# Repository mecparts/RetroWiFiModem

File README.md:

# Retro WiFi modem

## An ESP8266 based RS232 \<-\> WiFi modem with Hayes AT style commands and LED indicators

### (And yes, this version makes the noises)

This project grew out of a desire to get an old Ampro LB+/Z80 hooked up
to the Internet.

Right from the start, I knew I wanted a row of LED indicators at the
front of the modem so that it would be reminiscent of an old Hayes
Smartmodem. (I briefly considered finding an old Smartmodem on eBay, but
soon remembered that the case had in fact been made of metal; they don't
build 'em like that anymore.)

Since the modem was going to be hooked up to the Little Board's
serial port, I needed an actual RS-232 level serial port, with either a
DB-25 or DE-9 connector.

And finally, since I wanted the Hayes style LEDs, I thought it would be
handy to have the Hayes AT commands too, at least as close as I could
manage.

That was all I started with. I couldn't tell you how I stumbled across
the whole WiFi modem thing; I can't even remember what terms I searched
with but very quickly I came across the message thread at [WiFi232's
Evil
Clone](http://www.vcfed.org/forum/entry.php?740-WiFi232-s-Evil-Clone&bt=1056).
Inspired by that, and [Paul Rickards'
WiFi232](http://biosrhythm.com/?page_id=1453), and [Daniel Jameson's
ESP8266 based virtual modem](https://github.com/stardot/esp8266_modem) I
got started.

I had a preliminary version put together and working by the first
evening. Then the wholesale changes to the software began. And for the
longest time, it looked like they'd never end. Eventually though, they
calmed down and "wholesale changes" downshifted to "another tweak I'd
like to make."

The hardware didn't change nearly as much from beginning to end. I did
the development on a Wemos D1 R1 and a little half length solderless
breadboard mounted together. The plan for the final hardware was always
to use a [Wemos D1 mini](https://docs.wemos.cc/en/latest/d1/d1_mini.html).
A MAX3237 took care of the 3.3V <-> RS-232 level shifting, and a
74HCT245 was used to drive the indicator LEDs.

The only major additions to the hardware during development was an OR
gate on the serial output from the ESP8266 and the addition of a
DFPlayer Mini for the dialing and connection sounds.

On startup, the ESP8266 sends out some debug information
(at an oddball baud rate) through the serial port. It shows up as
garbage characters to whatever's hooked up to the serial port. It
annoyed me enough that I fed the Tx signal through the OR gate, with the
other input hooked up to an output pin that I could count on remaining
high (thereby masking off the Tx signal) until after the sketch had
started and set it low.

And while it didn't make the cut the first time around, there's a
DFPlayer Mini in this version for faux dialing and connection sounds.
They really do complete the whole retro feel (but they can be turned off
too).

## The Hardware

The second time around, I decided that I was going to bite the bullet
and go with some surface mount stuff, starting with the MAX3237. Having
a full suite of RS-232 control signals seemed worth it. I stuck with
through hole components where I could (I already had most of them in my
parts box) but adding the DFPlayer Mini meant that the 74HC32 and
74HCT245 had to be surface mount just to make them fit.

In keeping with the retro theme, the modem uses classic Hayes style
blinking LEDs and a DE-9F for the RS-232 connector. Everything is
displayed and brought out to the DE-9F connector: RTS, CTS, DSR, DTR,
DCD, RI, TxD and RxD.

The PCB is laid out for a
[Wemos D1 mini](https://docs.wemos.cc/en/latest/d1/d1_mini.html) and the
software expects to see just that. If you're just using the software and
not the PCB, there's no reason you couldn't use another kind of ESP8266
board; I used a D1 R1 myself when I was developing the modem. You'd just
need to add pin definitions for your board in RetroWiFiModem.h.

A separate 3.3V regulator is used to power the MAX3232 IC and 74HC32
quad OR gate. Some (most?) D1 mini clones have the smallest 3.3V
regulator on board that they can get away with to power the board, and
they don't have a lot of mA's left over to power anything else. Better
safe than sorry.

The power connector expects a 2.1mm I.D. x 5.5mm O.D. barrel plug,
delivering 5 volts, centre positive.  I used a Tri-Mag L6R06H-050 (5V,
1.2A), [DigiKey part#
364-1251-ND](https://www.digikey.com/product-detail/en/tri-mag-llc/L6R06H-050/364-1251-ND/7682614).
If you plug in a 9V adapter like you'd use for an Arduino, you *will*
let the magic smoke out and have an ex-modem on your hands.

On the off chance that there's someone else out there with a well
stocked parts box and a burning desire to put together their own WiFi
modem, there's a [BOM](kicad/RetroWiFiModem-bom.csv) in the kicad
sub directory. If you actually had to go out and buy all the parts, it
really wouldn't be cost effective.

Then again, how practical is getting an Ampro Little Board on the
Internet? Practicality isn't always everything. Sometimes nostalgia is
worth the effort.

## The case

Like I said at the start, I would have loved to have used an old Hayes
Smartmodem case, but they were metal and wouldn't have allowed the WiFi
to work particularly well.

In the end I went with a Hammond 1593N case (DigiKey part #
[HM963-ND](https://www.digikey.com/en/products/detail/hammond-manufacturing/1593NBK/1090774)
or [HM964-ND](https://www.digikey.com/en/products/detail/hammond-manufacturing/1593NGY/1090775)
depending on whether you like black or grey). STL and OpenSCAD
files are included for the front and back panels. You could use the
proper Hammond red panel for the front (DigiKey part #
[HM965-ND](https://www.digikey.com/en/products/detail/hammond-manufacturing/1593NIR10/1090776)),
*but* they're only available in 10 packs and their price is highway robbery.
I ended up using a slightly smaller red panel (DigiKey part #
[HM889-ND](https://www.digikey.com/en/products/detail/hammond-manufacturing/1593SIR10/409899))
that was ~much~ cheaper (it has recently increased in price by 500%)
and available in single units.

The labels are unbelievably low tech. I print them on a piece of inkjet
transparency film. I then cut that down to size so that it will fit
under the LED opening. Then I attach the trimmed down transparency piece
to a length of matte finish, invisible tape and carefully position it in
place. A bit of careful work with an x-acto knife and you've got
yourself a label that looks like it's part of the panel. If you look
closely at the front panel image you can see the edges of the
transparency film and the tape, but in practice they both essentially
disappear.

## The PCB

The PCB includes cutouts for the two columns that join the case
together, and mounting holes for the 6 standoffs. Also, there's an oddly
shaped cutout in back end to allow a particular IDC DE-9F I had on hand.
It's available from DigiKey (or a very close clone is) but it's fairly
pricey. But there's plenty of room for an ordinary solder cup DE-9F.
You'd most likely want to omit the 10 pin header and just wire the DE-9F
right to the board.

## The Software

In a nod to its popularity, the command set I used largely follows that
used in [Paul Rickards' WiFi232](http://biosrhythm.com/?page_id=1453)
modem. Even if the innards are completely different, it made sense to
make it *work* like what people were already used to. There's a reason
everyone's been copying the Hayes command set for almost 40 years!

### First time setup

The default serial configuration is 9600bps, 8 data bits, no parity, 1
stop bit.

Here's the commands you need to set up the modem to automatically
connect to your WiFi network:

1. `AT$SSID=your WiFi network name` to set the WiFi network that the
modem will connect to when it powers up.
2. `AT$PASS=your WiFi network password` to set the password for the
network.
3. `ATC1` to connect to the network.
4. Optional stuff:
   * `AT$SB=speed` to set the default serial speed.
   * `AT$SU=dps` to set the data bits, parity and stop bits.
   * `ATNETn` to select whether or not to use Telnet protocol.
   * `AT&Kn` to use RTS/CTS flow control or not.
   * `AT&Dn` to set up DTR handling.
5. `AT&W` to save the settings.

Once you've done that, the modem will automatically connect to your WiFi
network on power up and will be ready to "dial up" a connection with
ATDT.

### Command Reference

Multiple AT commands can be typed in on a single line. Spaces between
commands are allowed, but not within commands (i.e. AT S0=1 X1 Q0 is
fine; ATS 0=  1 is not). Commands that take a string as an argument
(e.g. AT$SSID=, AT$TTY=) assume that *everything* that follows is a part
of the string, so no commands are allowed after them.

Command | Details
------- | -------
+++     | Online escape code. Once your modem is connected to another device, the only command it recognises is an escape code of a one second pause followed by three typed plus signs and another one second pause, which puts the modem back into local command mode. The character used can be set with `ATS2=n`.
A/      | Repeats the last command entered. Do not type AT or press Enter.
AT      | The attention prefix that precedes all command except A/ and +++.
AT?     | Displays a help cheatsheet.
ATA     | Force the modem to answer an incoming connection when the conditions for auto answer have not been satisfied.
ATC?<br>ATC*n* | Query or change the current WiFi connection status. A result of 0 means that the modem is not connected to WiFi, 1 means the modem is connected. The command ATC0 disconnects the modem from a WiFi connection. ATC1 connects the modem to the WiFi.
ATDS*n* | Calls the host specified in speed dial slot *n* (0-9).
ATDT<i>[+=-]host[:port]</i> | Tries to establish a WiFi TCP connection to the specified host name or IP address. If no port number is given, 23 (Telnet) is assumed. You can also use ATDT to dial one of the speed dial slots in one of two ways:<br><br><ul><li>The alias in each speed dial slot is checked to see if it matches the specified hostname.</li><li>A host specified as 7 identical digits dials the slot indicated by the digit. (i.e. 2222222 would speed dial the host in slot 2).</li></ul>Preceding the host name or IP address with a +, = or - character overrides the ATNET setting for the period of the connection.<br><br><ul><li>**+** forces NET2 (fake Telnet)</li><li>**=** forces NET1 (real Telnet)</li><li>**-** forces NET0 (no Telnet)</li></ul>Once the dial attempt has begun, pressing any key before the connection is established will abort the attempt.
ATE?<br>ATE*n* | Command mode echo. Enables or disables the display of your typed commands.<br><br><ul><li>E0 Command mode echo OFF. Your typing will not appear on the screen.</li><li>E1 Command mode echo ON. Your typing will appear on the screen.</li></ul>
ATGET*http&#58;//host[/page]* | Displays the contents of a website page. **https** connections are not supported. Once the contents have been displayed, the connection will automatically terminate.
ATH | Hangs up (ends) the current connection.
ATI | Displays the current network status, including sketch build date, WiFi and call connection state, SSID name, IP address, and bytes transferred.
ATL?<br>ATL*n* | Query or set the volume of the speaker (0-3).
ATM?<br>ATM*n* | Query or set whether the speaker is enabled or disabled. ATM0 disables the speaker. ATM1 enables it.
ATNET?<br>ATNET*n* | Query or change whether telnet protocol is enabled. A result of 0 means that telnet protocol is disabled; 1 is *Real* telnet protocol and 2 is *Fake* telnet protocol. If you are connecting to a telnet server, it may expect the modem to respond to various telnet commands, such as terminal name (set with `AT$TTY`), terminal window size (set with `AT$TTS`) or terminal speed. Telnet protocol should be enabled for these sites, or you will at best see occasional garbage characters on your screen, or at worst the connection may fail.<br><br>The difference between *real* and *fake* telnet protocol is this: with *real* telnet protocol, a carriage return (CR) character being sent from the modem to the telnet server always has a NUL character added after it. The implementation of the telnet protocol used by some BBSes doesn't properly strip out the NUL character. When connecting to such BBSes (Particles! is one), use *fake* telnet.<br><br>When using *real* telnet protocol, when the telnet server sends a CR character followed by a NUL character, only the CR character will be sent to the serial port; the NUL character will be silently stripped out. With *fake* telnet protocol, the NUL will be passed through.
ATO | Return online. Use with the escape code (+++) to toggle between command and online modes.
ATQ?<br>ATQ*n* | Enable or disable the display of result codes. The default is Q0.<br><br><ul><li>Q0 Display result codes.</li><li>Q1 Suppress result codes (quiet).</li></ul>
ATRD<br>ATRT | Displays the current UTC date and time from NIST in the format *YY-MM-DD HH:MM:SS*. A WiFi connection is required and you cannot be connected to another site.
ATS0?<br>ATS0=*n* | Display or set the number of "rings" before answering an incoming connection. Setting `S0=0` means "don't answer".
ATS2?<br>ATS2=*n* | Display or set the ASCII code used in the online escape sequence. The default value is 43 (the + plus character). Setting it to any value between 128 and 255 will disable the online escape function.
ATV?<br>ATV*n* | Display result codes in words or numbers. The default is V1.<br><br><ul><li>V0 Display result codes in numeric form.</li><li>V1 Display result codes in text form.</li></ul>
ATX?<br>ATX*n* | Control the amount of information displayed in the result codes. The default is X1 (extended codes).<br><br><ul><li>X0 Display basic codes (CONNECT, NO CARRIER)</li><li>X1 Display extended codes (CONNECT speed, NO CARRIER (connect time))</li></ul>
ATZ | Resets the modem.
AT&F | Reset the NVRAM contents and current settings to the sketch defaults. All settings, including SSID name, password and speed dial slots are affected.
AT&D?<br>AT&D*n* | Display or set the handling of DTR going inactive. The default is &D0 (ignored).<br><br><ul><li>&D0 Ignore</li><li>&D1 Go to command mode</li><li>&D2 End call</li><li>&D3 Reset modem</li></ul>
AT&K?<br>AT&K*n* | Data flow control. Prevents the modem's buffers for received and transmitted from overflowing.<br><br><ul><li>&K0 Disable data flow control.</li><li>&K1 Use hardware flow control. Requires that your computer and software support Clear to Send (CTS) and Request to Send (RTS) at the RS-232 interface.</li></ul>
AT&R?<br>AT&R=*server pwd* | Query or change the password for incoming connections. If set, the user has 3 chances in 60 seconds to enter the correct password or the modem will end the connection.
AT&V*n* | Display current or stored settings.<br><br><ul><li>&V0 Display current settings.</li><li>&V1 Display stored settings.</li></ul>
AT&W | Save current settings to NVRAM.
AT&Zn?<br>AT&Z*n*=*host[:port],alias* | Store up to 10 numbers in NVRAM, where *n* is the position 0-9 in NVRAM, and *host[:port]* is the host string, and *alias* is the speed dial alias name. The host string may be up to 50 characters long, and the alias string may be up to 16 characters long.<br><br>Example: `AT&Z2=particlesbbs.dyndns.org:6400,particles`<br><br>This number can then be dialed in any of the following ways:<br><br><ul><li>`ATDS2`</li><li>`ATDTparticles`</li><li>`ATDT2222222`</li></ul>
AT$AE?<br>AT$AE=*startup AT cmd* | Query or change the command line to be executed when the modem starts up.
AT$AYT | Sends a Telnet "Are You There?" command if connected to a Telnet remote.
AT$BM?<br>AT$BM=*server busy msg* | Query or change a message to be returned to an incoming connection if the modem is busy (i.e. already has a connection established).
AT$MDNS<br>AT$MDNS=*mDNS name* | Query or change the mDNS network name (defaults to "espmodem"). When a non zero TCP port is defined, you can telnet to that port with **telnet mdnsname.local port**.
AT$PASS?<br>AT$PASS=*WiFi pwd* | Query or change the current WiFi password. The password is case sensitive. Clear the password by issuing the set command with no password. The maximum length of the password is 64 characters.
AT$SB?<br>AT$SB=*n* | Query or change the current baud rate. Valid values for "n" are 110, 300, 450, 600, 710, 1200, 2400, 4800, 9600, 19200, 38400, 57600, 76800 and 115200. Any other value will return an ERROR message. The default baud rate is 1200. The Retro WiFi modem does not automatically detect baud rate like a dial-up modem. The baud rate setting must match that of your terminal to operate properly. It will display garbage in your terminal otherwise.
AT$SP?<br>AT$SP=*n* | TCP server port to listen on. A value of 0 means that the TCP server is disabled, and no incoming connections are allowed.
AT$SSID?<br>AT$SSID=*ssid name* | Query or change the current SSID to the specified name. The given SSID name is case sensitive. Clear the SSID by issuing the set command with no SSID. The maximum length of the SSID name is 32 characters.
AT$SU?<br>AT$SU=*dps* | Query or change the current number of data bits ('d'), parity ('p') and stop bits ('s") of the serial UART. Valid values for 'd' are 5, 6, 7 or 8 bits. Valid values for 'p' are (N)one, (O)dd or (E)ven parity. Valid values for 's' are 1 or 2 bits. The default settings are 8N1. The UART setting must match your terminal to work properly.
AT$TTL?<br>AT$TTL=*telnet location* | Query or change the Telnet location value to be returned when the Telnet server issues a SEND-LOCATION request. The default value is "Computer Room".
AT$TTS?<br>AT$TTS=*WxH* | Query or change the window size (columns x rows) to be returned when the Telnet server issues a NAWS (Negotiate About Window Size) request. The default value is 80x24. For terminals that are smaller than 80x24, setting these values appropriately will enable paging on the help (AT?) and network status (ATI) commands.
AT$TTY?<br>AT$TTY=*terminal type* | Query or change the terminal type to be returned when the Telnet server issues a TERMINAL-TYPE request. The default value is "ansi".
AT$W?<br>AT$W=*n* | Startup wait.<br><br><ul><li>$W=0 Startup with no wait.</li><li>$W=1 Wait for the return key to be pressed at startup.</li></ul>

### Updating the Software

While I liked the idea of being able to update the software OTA, it
seemed to make more sense in my situation to be able to *push* a new
version as I built it rather than have the modem *pull* it. So that's
what I did. It uses the default OTA upload capability built into the
Arduino IDE.

**Jan 24/22:** It's been reported that the ESP8266 core is slightly
snafu'd at the moment, and that it's breaking things in the modem
software. As a workaround, I've added the bin file that gets uploaded
to the modem in the repository. I haven't updated my ESP8266 core in
ages; "if it isn't broken, don't break it", and everything still works
for me. The bin file can be uploaded with the *espota.py* tool in the
ESP8266 tool directory tree.

(If TPTB have deleted/renamed/moved that tool in the current core,
you'll have to figure out how to do a manual OTA update.)

### RTS/CTS handshaking and a dead spin loop issue

Something I noticed with ESP8266 software that puzzled me was the
number of places I saw a series of Serial print statements being broken
up with calls to yield(), like so:

```
   Serial.print("Hello world!\n");
   yield();
   Serial.print("How are you today?\n");
   yield();
```
It didn't take long to figure out what was going on; The print() call
was blocking, and at lower baud rates, even printing a few relatively
short strings was enough to cause the watchdog to bark and cause a
reset. So the repetitive yield() calls were an attempt to feed the
watchdog often enough to keep it from barking.

What does this have to do with RTS/CTS handshaking? Simply put,
lowering RTS for more than a few seconds was causing the watchdog to
bark as well. So I started digging.

In cores/esp8266/uart.cpp I found the following function:

```
static void
uart_do_write_char(const int uart_nr, char c)
{
    while(uart_tx_fifo_full(uart_nr));

    USF(uart_nr) = c;
}
```

This is the low level function that everything calls to send a character
out the serial port. The cause of the watchdog barking is in the dead
spin while loop. It waits until there's room in the transmit FIFO to add
another character. So if RTS/CTS handshaking is enabled, and RTS is low
for longer than the watchdog likes: woof.

What I did to quiet the watchdog down both when sending long strings at
low baud rates and during long waits for RTS to come active again was to
add a yield() call to the dead spin while loop, like so:

```
static void
uart_do_write_char(const int uart_nr, char c)
{
    while(uart_tx_fifo_full(uart_nr))
      yield();

    USF(uart_nr) = c;
}
```

This way, no matter how long the code has to wait for space in the
transmit FIFO, the watchdog is kept well fed and quiet.

## Status

As I said way back in 2020, is a personal project like this ever
*really* finished? I've had two units assembled and in use since the
spring of 2020, and a third since 2022, and while there's
been some software changes since then, and a second rev of the hardware
to bring out all the RS-232 control signals and add in the faux dialing
and connections sounds, I really don't expect any more changes. But I've
said that before! There are no outstanding bugs that I'm aware of, and
no new features on my wish list. For the time being at least, I think
it's complete.

### Linux, Telnet, Zmodem and downloading binary files

Have you used the modem to 'dial' into a Linux box? And have you done a
`sz binary_file` on the Linux box? And at a completely reproducible
point in the file, has the connection dropped? But other binary files
work just fine? Then read on.

This drove me slightly batty for months. I finally narrowed it down to
trying to send blocks of binary data with a large number of FF bytes. I
eventually created a test file consisting of 2K of FF and used that to
test with. I could download it through the modem with Xmodem just fine.
Ymodem also worked if I kept the block size down to 128 bytes - but the
connection would drop instantly if I tried sending 1K blocks. Same thing
with Zmodem.

In fact, if I just tried `cat binary_file`, the connection would
drop. Which eventually got me thinking. Sitting at the console on my
main Linux box, I telnet'd to the same box and logged in. No WiFi modem
involved anywhere, just a telnet session on the console to the same box.
I then did a `cat binary_file`. The telnet connection dropped, and I
was back in my original session.

It's the Linux telnet daemon. Not the modem at all.

To prove it to myself, I hooked up WiFi modems to two systems on their
serial ports and had one dial into the other. I could send the all FF
binary file back and forth with Zmodem and Ymodem, no trouble at all.

But you really, really need to download that binary file through the
modem from a telnet connection to a Linux box? You're not going to be
able to use Zmodem. Ymodem will work (the sy command defaults to 128
byte blocks), as will Xmodem. But not Zmodem.

Oddly enough, the telnet daemon has no trouble *receiving* the all FF
binary file. Only sending it. Your guess as to why is probably better
than mine.

## References

* [WiFi232 - An Internet Hayes Modem for your Retro Computer](http://biosrhythm.com/?page_id=1453)<br>
* [WiFi232's Evil Clone](https://forum.vcfed.org/index.php?threads/wifi232s-evil-clone.1070412/)<br>
* [Jussi Salin's Virtual modem for ESP8266](https://github.com/jsalin/esp8266_modem)<br>
* [Stardot's ESP8266 based virtual modem](https://github.com/stardot/esp8266_modem)<br>
* [Roland Juno's ESP8266 based virtual modem](https://github.com/RolandJuno/esp8266_modem)

## Acknowledgements

* A whole lot of people owe a big vote of thanks to Jussi Salin for
releasing their virtual modem code for the ESP8266 and starting the
ball rolling.
* Paul Rickards for an amazing bit of hardware to draw inspiration from.
* All the Stardot contributors for their work.
* And, of course, Dennis C. Hayes for creating something so simple and
elegant that has stood the test of time.

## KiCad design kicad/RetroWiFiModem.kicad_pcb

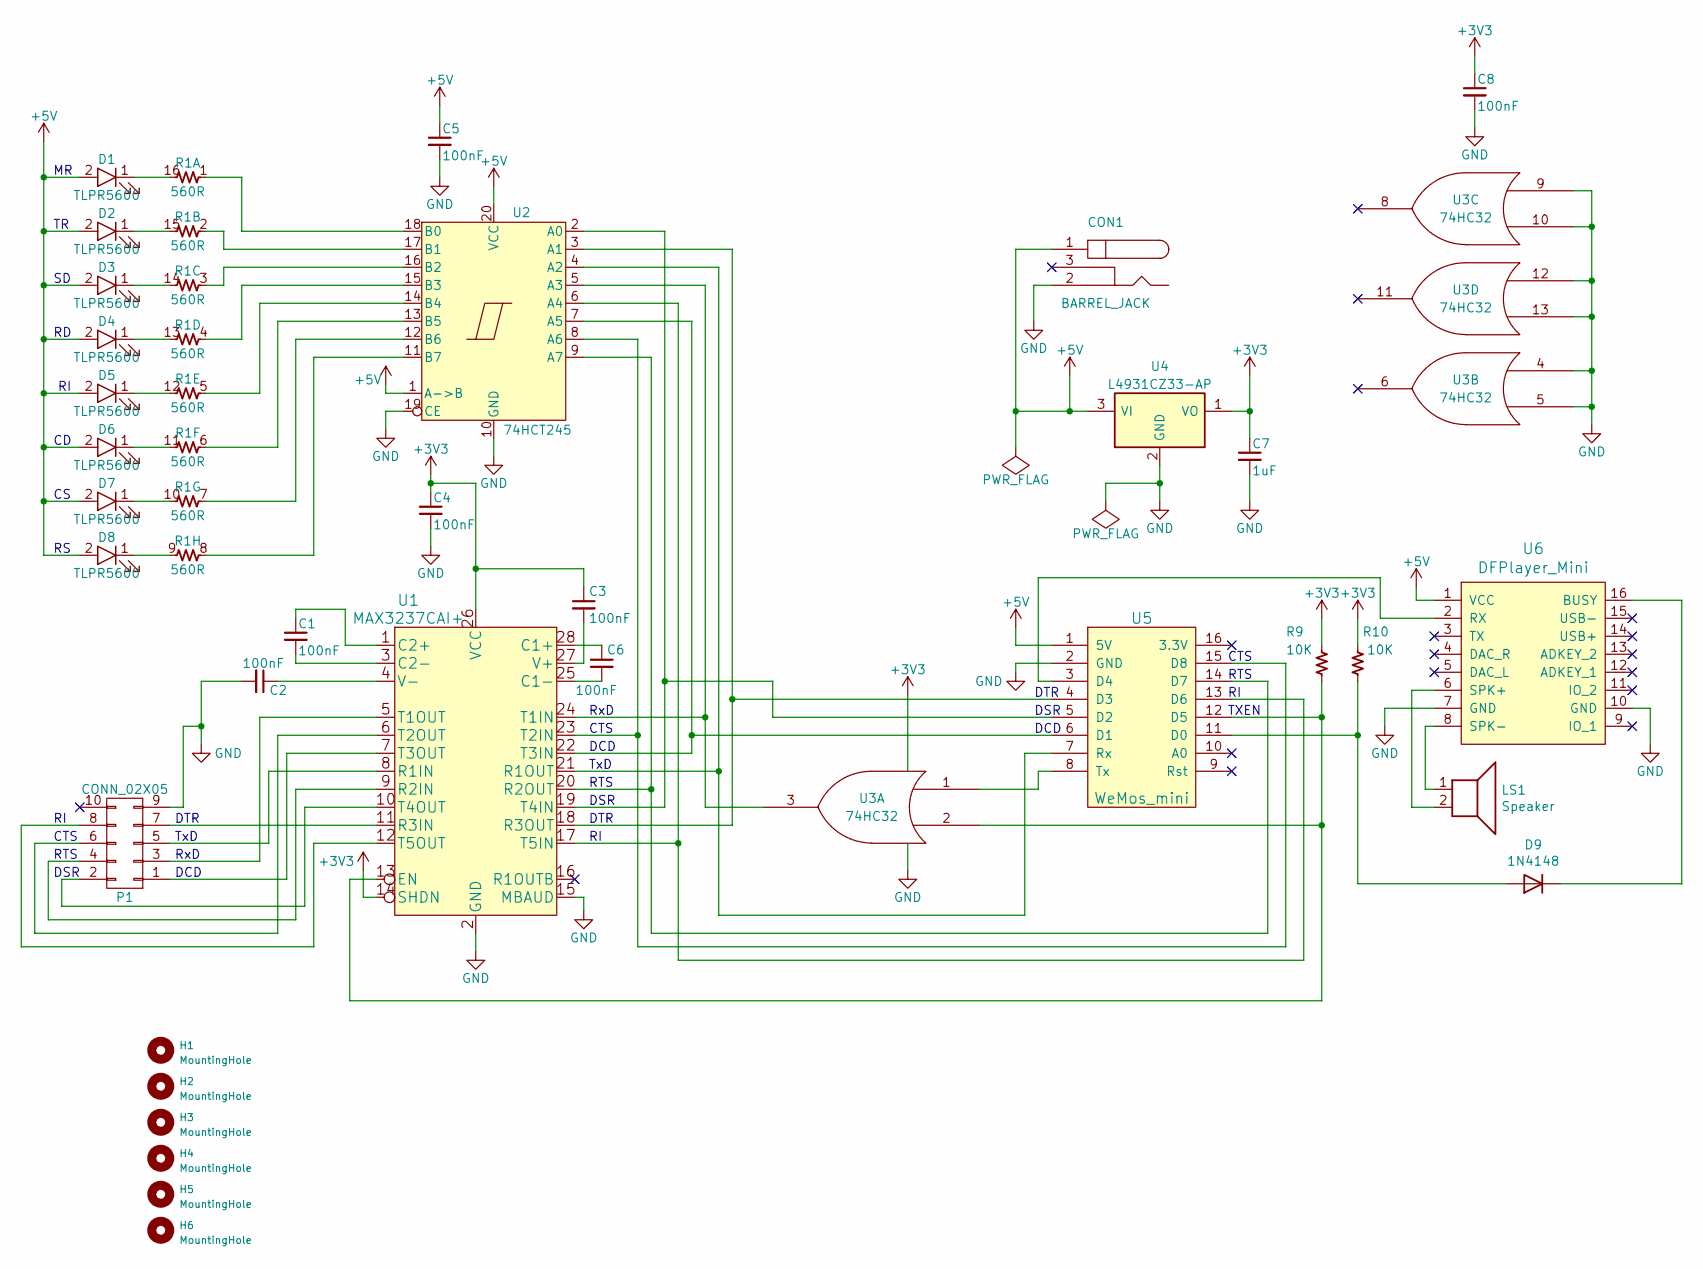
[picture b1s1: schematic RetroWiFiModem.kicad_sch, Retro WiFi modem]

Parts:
C1, C2, C3, C4, C5, C8: 100nF; C_Disc_D3_P2.5; DigiKey PN 399-9859-1-ND
C6: 100nF; R3; DigiKey PN 399-9843-ND
C7: 1uF; C_Disc_D3_P2.5; DigiKey PN 399-3529-ND
CON1: BARREL_JACK; BarrelJack_Horizontal; DigiKey PN 839-54-00166-ND
D1, D2, D3, D4, D5, D6, D7, D8: TLPR5600; LED-3MM; DigiKey PN TLPR5600-ND
D9: 1N4148; D_DO-35_SOD27_P7.62mm_Horizontal
H1, H2, H3, H4, H5, H6: MountingHole; MountingHole_3.2mm
LS1: Speaker; PinHeader_1x02_P2.54mm_Vertical
P1: CONN_02X05; IDC_Header_Straight_10pins; DigiKey PN ED1543-ND
R1: 560R; DIP-16_W7.62mm_LongPads; DigiKey PN CF18JT560RCT-ND
R9, R10: 10K; R3; DigiKey PN CF18JT10K0CT-ND
U1: MAX3237CAI+; SOIC-28W_7.5x17.9mm_Pitch1.27mm
U2: 74HCT245; SOIC-20W_7.5x12.8mm_P1.27mm
U3: 74HC32; SOIC-14_3.9x8.7mm_P1.27mm; DigiKey PN 296-1589-5-ND
U4: L4931CZ33-AP; TO-92_Inline_Wide; DigiKey PN LP2950ACZ-3.3GOS-ND
U5: WeMos_mini; wemos-d1-mini-with-pin-header-and-connector
U6: DFPlayer_Mini; DFPlayerMini

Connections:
+3V3: C3.1, C4.1, C7.1, C8.1, R9.1, R10.1, U1.14 (SHDN), U1.26 (VCC), U3.14 (VCC), U4.1 (VO)
+5V: C5.1, CON1.1, D1.2 (A), D2.2 (A), D3.2 (A), D4.2 (A), D5.2 (A), D6.2 (A), D7.2 (A), D8.2 (A), U2.1 (A->B), U2.20 (VCC), U4.3 (VI), U5.1 (5V), U6.1 (VCC)
GND: C2.2, C4.2, C5.2, C7.2, C8.2, CON1.2, P1.9, U1.2 (GND), U1.15 (MBAUD), U2.10 (GND), U2.19 (CE), U3.4, U3.5, U3.7 (GND), U3.9, U3.10, U3.12, U3.13, U4.2 (GND), U5.2 (GND), U6.7 (GND), U6.10 (GND)
unnamed: C1.1, U1.1 (C2+)
unnamed: C1.2, U1.3 (C2-)
unnamed: C2.1, U1.4 (V-)
unnamed: C3.2, U1.27 (V+)
unnamed: C6.1, U1.28 (C1+)
unnamed: C6.2, U1.25 (C1-)
unnamed: D1.1 (K), R1.16 (R1.2)
unnamed: D2.1 (K), R1.15 (R1.2)
unnamed: D3.1 (K), R1.14 (R1.2)
unnamed: D4.1 (K), R1.13 (R1.2)
unnamed: D5.1 (K), R1.12 (R1.2)
unnamed: D6.1 (K), R1.11 (R1.2)
unnamed: D7.1 (K), R1.10 (R1.2)
unnamed: D8.1 (K), R1.9 (R1.2)
unnamed: D9.1 (K), U6.16 (BUSY)
unnamed: D9.2 (A), R10.2, U5.11 (D0)
unnamed: LS1.1, U6.8 (SPK-)
unnamed: LS1.2, U6.6 (SPK+)
unnamed: P1.1, U1.7 (T3OUT)
unnamed: P1.2, U1.10 (T4OUT)
unnamed: P1.3, U1.5 (T1OUT)
unnamed: P1.4, U1.9 (R2IN)
unnamed: P1.5, U1.8 (R1IN)
unnamed: P1.6, U1.6 (T2OUT)
unnamed: P1.7, U1.11 (R3IN)
unnamed: P1.8, U1.12 (T5OUT)
unnamed: R1.1 (R1.1), U2.18 (B0)
unnamed: R1.2 (R1.1), U2.17 (B1)
unnamed: R1.3 (R1.1), U2.16 (B2)
unnamed: R1.4 (R1.1), U2.15 (B3)
unnamed: R1.5 (R1.1), U2.14 (B4)
unnamed: R1.6 (R1.1), U2.13 (B5)
unnamed: R1.7 (R1.1), U2.12 (B6)
unnamed: R1.8 (R1.1), U2.11 (B7)
unnamed: R9.2, U1.13 (EN), U3.2, U5.12 (D5)
unnamed: U1.17 (T5IN), U2.6 (A4), U5.13 (D6)
unnamed: U1.18 (R3OUT), U2.3 (A1), U5.4 (D3)
unnamed: U1.19 (T4IN), U2.2 (A0), U5.5 (D2)
unnamed: U1.20 (R2OUT), U2.9 (A7), U5.14 (D7)
unnamed: U1.21 (R1OUT), U2.4 (A2), U5.7 (Rx)
unnamed: U1.22 (T3IN), U2.7 (A5), U5.6 (D1)
unnamed: U1.23 (T2IN), U2.8 (A6), U5.15 (D8)
unnamed: U1.24 (T1IN), U2.5 (A3), U3.3
unnamed: U3.1, U5.8 (Tx)
unnamed: U5.3 (D4), U6.2 (RX)

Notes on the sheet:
DCD
CTS
DSR
TxD
DTR
RxD
RTS
TXEN

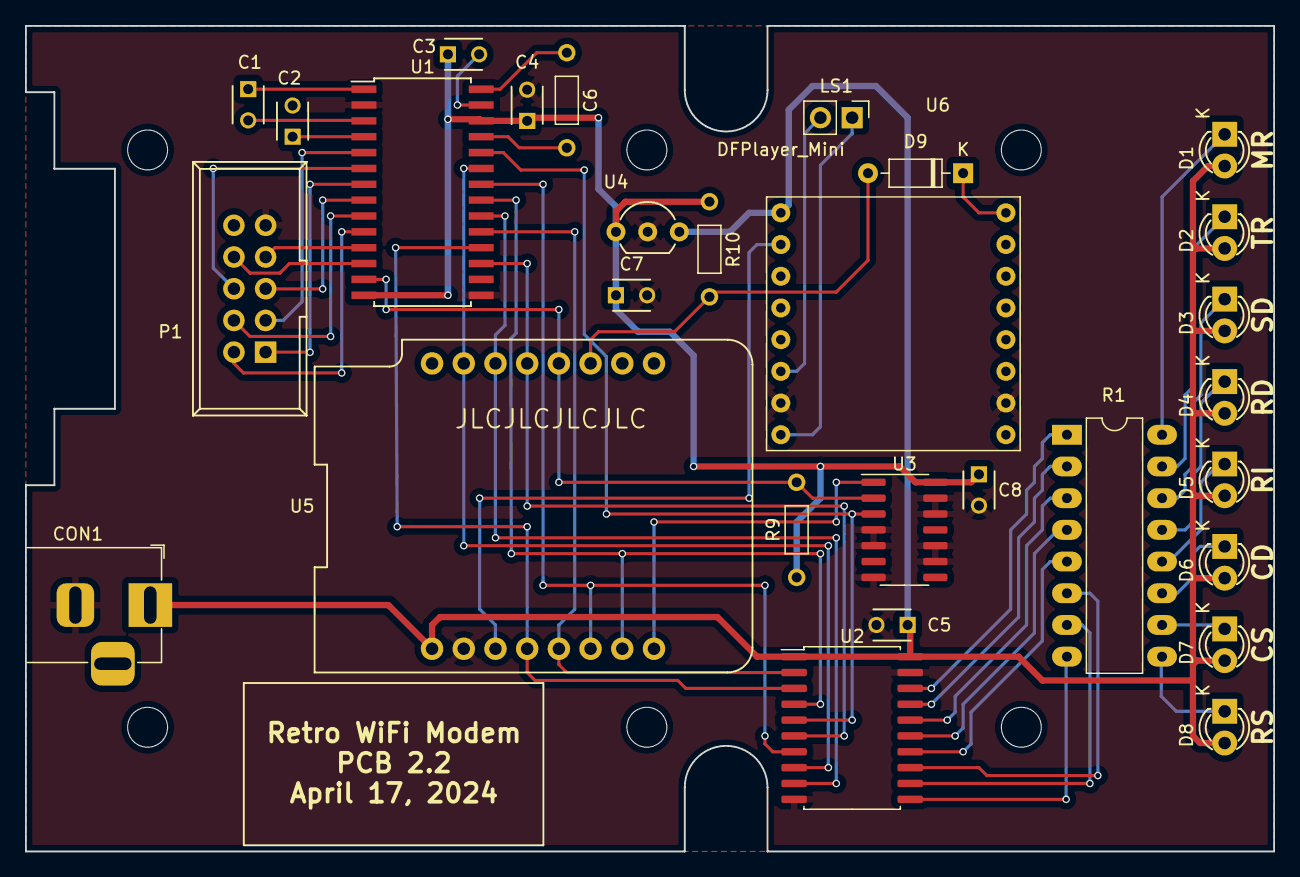
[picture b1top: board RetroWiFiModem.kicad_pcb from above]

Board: 2 copper layers, 100.0 x 66.1 mm, 35 parts (0 on the bottom side), 48 nets.

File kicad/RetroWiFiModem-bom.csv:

Reference,Quantity, Value, DigiKey PN,BC-Robotics PN
P1,1,CONN_02X05,ED1543-ND,
U3,1,SN74HC32DR,296-1199-1-ND,
U4,1,L4931CZ33-AP,LP2950ACZ-3.3GOS-ND,
D3-D8,8,TLPR5600,TLPR5600-ND,
"C1-C2,C4-C6,C8",6,100nF,399-9859-1-ND,
C7,1,1uF,399-3529-ND,
CON1,1,BARREL_JACK,839-54-00166-ND,
R1,8,560R,CF18JT560RCT-ND,
R9-R10,2,10K,CF18JT10K0CT-ND,
U1,1,MAX3237ECDWR,296-36945-1-ND,
U2,1,74HCT245D,74HCT245DCT-ND,
C3,1,100nF,399-9859-1-ND,
U5,1,WeMos_mini,,
U6,1,DFPlayer_Mini,1738-1041-ND,
LS1,1,Speaker,,AUD-013
D9,1,1N4148,1N4148FS-ND,
,1,Hammond 1593NBK case,HM963-ND ,
,1,Hammond red panel,HM889-ND ,
,50,PCB screws,HM1442-ND,
,1,5V wall adapter,364-1251-ND ,
,1,DE-9F IDC connector,5746861-4-ND,
,2,4-40 hex standoffs,A104867-ND,
,4,8 pos machine pin socket,2057-SMC-1-08-1-GT-ND,
,1,10 pos IDC socket,1175-1443-ND ,
,1,10 cond ribbon cable,3M157815-1-ND,

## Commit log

2020-04-26 Touch-ups in README.md
2020-04-26 More tweaks to README.md
2020-04-26 More README.md tweaks, and added in the forgotten license file.
2020-04-26 More README.md corrections.
2020-04-26 Correcting a link error in the readme.
2020-04-27 Updated list of valid speeds in README.md
2020-04-28 Added a section on my modification to the uart.cpp file in the ESP8266 core to keep the watchdog fed and happy during long waits for space in the serial transmit FIFO.
2020-04-30 Reformatted AT commands into a table.
2020-04-30 README.md touchup
2020-04-30 More README.md touchups
2020-04-30 Improved lists in tables in README.md
2020-06-25 Got baud rate change working with the modem returning a status result now, so it's been finally added in.
2020-07-04 Found a cleaner way to change the serial baud rate using Serial.updateBaudRate And discovered that the "latest" documentation does not mean that it's the documentation for the "latest" software! Foun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
2020-07-08 Added baud rate to ATI command.
2020-07-19 Auto switch telnet mode option on session basis. ATDTnumber will use the currently defined telnet mode. ATDT+number will use NET2 for the session and return to the defined telnet mode when the sessio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
2020-07-19 Updated README.md with the latest changes to the ATDT command.
2020-07-19 Twiddling with Markdown formatting...
2020-07-19 More Markdown fiddling...
2020-07-19 Abandom Markdown, try HTML.
2020-07-19 Refining formatting.
2020-08-01 Added auto 'ATNET2' setting to Particles! speed dial
2020-08-03 Minor changes to README.md
2020-08-03 Added a .gitignore file
2020-08-03 Missed a ! in the AT$TTL command handling.
2020-08-11 Allow aborting a dial command with any keypress I noticed that the terminal program I'm using would send a CR when it tried to abort a pending dial command. Thinking back to a real dialup modem, I va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
2020-08-14 Updated README.md to include the abort dial capability in ATDT.
2020-08-24 Added a picture of the original prototype to the readme file.
2020-09-29 update symbols and footprints for KiCad 5.1.2
    * remaps all symbols and footprints to those present in KiCad 5.1.2.
    * add mounting holes to schematics
    * PCB has been touched up due to footprint changes, but should remain
    almost identical to the original
    * NOTE: schematic now has some warnings about tristate<->output connections
    symbols and footprints are mapped as follows:
2020-10-02 Renamed KiCad4 files as "-kicad4" for upcoming pull.
2020-10-02 Revert "Renamed KiCad4 files as "-kicad4" for upcoming pull."
    This reverts commit bb5cc11a9b487fb4e979007bafb8acc164f68607.
2020-10-02 Trying to re-can a can of worms...
2020-10-02 One more worm to re-can...
2020-10-05 Race condition with '+++' and remote ending connection fixed. Timing is everything: discovered that if I typed the escape sequence +++ and the remote end dropped the connection within the 1 second gu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
2020-11-25 Command buffer needs to be emptied on error in quiet mode In non-quiet, when an ERROR is returned, the command buffer was emptied. In quiet, nothing would happen, the code would go into an infinite l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
2020-11-26 Tracked down a bug with ASCII text at higher baud rates There's been a long standing problem with sending ASCII text (serial -> WiFi) in file transfers. Above 4.8K, it just wouldn't hardly ever work.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
    There's more testing to be done but I've already done
    batch Ymodem sends at 38.4K and that's the first time
    I'm had those working that fast.
2020-12-03 Added 'Linux, Telnet, Zmodem and binary files' section to README
2020-12-03 Updated the status and moved it towards the end of the README
2021-03-22 Server on telnet port (23) now works with Linux client A mini pandemic project: I sat down and figured out what was required to have the modem code work with the the telnet options that the Linux tel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
2021-04-21 Added paging to the help (AT?) and network status (ATI) commands. I have an old SSM VB1 video board (64 columns by 16 rows) and decided to add output paging so that the text wouldn't scroll off the s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
2021-06-03 Minor tweaks to README.md
2021-08-18 Suppress extended code display when quiet mode enabled
2021-12-21 Removed a couple of duplicated items in the help text.
2022-01-24 Added binary file for manual OTA upload.
2022-04-15 Updated a link due to link rot.
2022-04-24 Minor README.md update
2022-09-20 Fixed a spelling mistake.
2022-09-29 Added code to request character mode on manual (ATA) answer. As a learning exercise, I've been porting the code to a Raspberry Pi Pico W. Aside from the earlier spelling mistake, this is the first "o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
2022-09-29 Replacing tabs that had snuck into the source a while back.
2022-10-01 Added Hayes-style S2 (online escape sequence character) support. Discovered during more Pico W wifi modem testing that when connected to another wifi modem, a +++ sequence would put both ends in comm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
2022-10-02 Endless loop of Telnet commands when 2 modems connected together. Another "found it while debugging the Pico W" code bug. A wifi modem dialled into another wifi modem would result in an endless loop 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
2022-10-11 Tightened up inter char spacing in online escape sequence.
2022-10-17 Added Telnet "Are You There?" support
2022-10-17 Fixed a "been there forever" bug in ATH. Not fatal, but annoying.
2023-03-15 Initial commit for the v2 hardware. * MAX3237 for full suite of RS-232 control signals * DFPlayer Mini for faux dialing and connection sounds * Gerbers suitable for JLCPCB included
2023-03-15 Cleaning up old files
2023-03-15 Overlooked that .WAV files were symlinks
2023-03-20 Added some support for a particular MUD server
2023-03-22 Increased the intermediate volume levels (ATL1 & ATL2) to be better heard through the case.
2023-03-22 Added updated .bin file
2023-06-10 Added the label PDF file and a "how to use it" bit in the readme.
2023-06-10 Added note on price increase on red LED panel
2024-08-14 Updated to KiCad 6.0
2024-08-14 Completed KiCad 6.0 updates
2024-08-14 Recompiled with all warnings enabled; pruned out some dead code and fixed a few "that's mostly harmless but not right" bits.
2024-08-24 Modified a handful of instances using millis for delays where there was the minute possibility of wrap around. Also increased the delay between the end of the dialing DTMF tones and the first ring.
2024-08-24 Added current .bin file
2024-08-29 Modified the dialling sound code to abort early if a key press is detected. What can I say; it's a cold, rainy day and I was bored!
2026-04-14 DTR transition wasn't being cleared on answering an incoming call. First bug in 2 years. I hooked a modem up to a system with all the control lines and enabled DTR dropping to end a call. The system 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
    Also, time.nist.gov has been having issues all year, so I've
    routed to a specific NIST host.
